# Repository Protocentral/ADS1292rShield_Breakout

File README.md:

ProtoCentral ADS1292R ECG/respiration shield and breakout board 
================================

[  
Dont have it yet? But one here: ADS1292R ECG/Respiration Shield for Arduino- v2 (PC-4128)](https://protocentral.com/product/ads1292r-ecg-respiration-shield-for-arduino-v2/)

[  
Dont have it yet? But one here: ADS1292R ECG/Respiration Breakout for Arduino- v3 (PC-4116)](https://protocentral.com/product/ads1292r-ecg-respiration-breakout-kit/)

The Arduino library for this product is now available in the **[ProtoCentral ADS1292R Arduino Library repo](https://github.com/Protocentral/protocentral-ads1292r-arduino)**

**Breakout v4:** KiCad design files and the schematic PDF are in [`hardware/breakout/v4`](hardware/breakout/v4). v4 has a new 10-pin host header (CS, MOSI, SCK, MISO, DRDY, START, RST, CLK, VCC, GND) with the ADS1292R clock brought out, so the pinout below applies to v3 only. Earlier revisions remain in `hardware/breakout` and `hardware/shield`.

Easily monitor ECG and respiration using your Arduino with this plug-in shield. The version 2 of this product adds a new SPI pin header making it compatible with newer Arduino devices including the Arduino Yun and 3.5mm connector for the electrodes. We now include the electrodes and cable also with the shield

Just plug it into an Arduino and you're ready to go. The 3.5 mm circular connector provides an easy way to connect electodes to the shield. The other end of this cable has snaps for standard ECG electrodes. We also include a pakc of 10 disposable EG electrodes. It accepts two ECG electrodes and one Driven Right Leg (DRL) electrode for common mode noise reduction. 

Another interesting feature of this shield is that you can also measure the respiratory activity using the same two electrodes connected to the shield. The ADS1292R uses a method known as impedance pneumography to measure respiration using the changes in chest impedance caused during respiration. 

Features:
----------
* ADS1292R Analog Front End IC
* Onboard 3.3V voltage regulator for low noise
* Onboard logic level transalators for Arduino interface
* Prototyping area for adding addtional components

Includes:
----------
* ADS1292R Arduino shield
* Electrode cable with 3.5mm connector and ECG electrodes connectors
* Pack of 10 disposable stick-on ECG electrodes.

Connecting the shield to your Arduino
-------------------------------------
Connect the ECG/Respiration shield to the Arduino by stacking it on top of your Arduino. This shield uses the SPI interface  to communicate with the Arduino. Since this includes the ICSP header, which is used on newer Arduinos for SPI communication,  this shield is also compatible newer Arduino boards such as the Arduino Yun and Due.
 
Wiring the Breakout to your Arduino
------------------------------------
 If you have bought the breakout the connection with the Arduino board is as follows:
 
|ads1292r pin label| Arduino Connection   |Pin Function      |
|----------------- |:--------------------:|-----------------:|
| VDD              | +5V                  |  Supply voltage  |             
| PWDN/RESET       | D4                   |  Reset           |
| START            | D5                   |  Start Input     |
| DRDY             | D6                   |  Data Ready Outpt|
| CS               | D7                   |  Chip Select     |
| MOSI             | D11                  |  Slave In        |
| MISO             | D12                  |  Slave Out       |
| SCK              | D13                  |  Serial Clock    |
| GND              | Gnd                  |  Gnd             |
 
Installing the Arduino libraries 
---------------------------------
Arduino library for this boards is now available at https://github.com/Protocentral/protocentral-ads1292r-arduino or from the Arduino Library Manager inside the Arduino IDe. 

If you have correctly installed the libraries, the example sketeches should now be available from within Arduino at File-->Examples-->ProtoCentral ADS1292R library.

Using the ProtoCentral OpenView GUI
-----------------------------------

The GUI for visualizing the ECG and Respiration as well as parameters like Heart rate and Respiration rate is written in Processing, based on Java and is cross-compilable across platforms. 
 
Java 8 is required on all platforms for running the processing-based GUI application. You can download Java for your platform from the [Official Java website](https://java.com/en/download/).

You can download and install [ProtoCentral OpenView](https://github.com/Protocentral/protocentral_openview) from here: https://github.com/Protocentral/protocentral_openview

Connecting the ECG Electrodes
------------------------------
 A 3-electrode cable along with a standard stereo jack is provided along with the shield to connect the electrodes to the     shield. The electrode input connector is highlighted in the below picture.
 
 The other side of the electrode connector would connect to snap-on electrodes attached to the body. For testing purposes,    you can use an ECG simulator to provide inputs to the board. 

 Warning:
 When connecting the electodes to the body, it is safer to disconnect the mains power source to the Arduino. For example, if  you are using the Arduino along with a laptop, disconnecting the battery charger from the laptop would be a safe option.
 
Placing the Electrodes on the body
---------------------------------

License Information
===================
This product is open source! 

Both, our hardware and software are open source and licensed under the following licenses:

Hardware
---------

**All hardware is released under the [CERN-OHL-P v2](https://ohwr.org/cern_ohl_p_v2.txt)** license.

Copyright CERN 2020.

This source describes Open Hardware and is licensed under the CERN-OHL-P v2.

You may redistribute and modify this documentation and make products
using it under the terms of the CERN-OHL-P v2 (https:/cern.ch/cern-ohl).
This documentation is distributed WITHOUT ANY EXPRESS OR IMPLIED
WARRANTY, INCLUDING OF MERCHANTABILITY, SATISFACTORY QUALITY
AND FITNESS FOR A PARTICULAR PURPOSE. Please see the CERN-OHL-P v2
for applicable conditions

Software
--------

**All software is released under the MIT License(http://opensource.org/licenses/MIT).**

THE SOFTWARE IS PROVIDED "AS IS", WITHOUT WARRANTY OF ANY KIND, EXPRESS OR IMPLIED, INCLUDING BUT NOT LIMITED TO THE WARRANTIES OF MERCHANTABILITY, FITNESS FOR A PARTICULAR PURPOSE AND NONINFRINGEMENT. IN NO EVENT SHALL THE AUTHORS OR COPYRIGHT HOLDERS BE LIABLE FOR ANY CLAIM, DAMAGES OR OTHER LIABILITY, WHETHER IN AN ACTION OF CONTRACT, TORT OR OTHERWISE, ARISING FROM, OUT OF OR IN CONNECTION WITH THE SOFTWARE OR THE USE OR OTHER DEALINGS IN THE SOFTWARE.

Documentation
-------------
**All documentation is released under [Creative Commons Share-alike 4.0 International](http://creativecommons.org/licenses/by-sa/4.0/).**

You are free to:

* Share — copy and redistribute the material in any medium or format
* Adapt — remix, transform, and build upon the material for any purpose, even commercially.
The licensor cannot revoke these freedoms as long as you follow the license terms.

Under the following terms:

* Attribution — You must give appropriate credit, provide a link to the license, and indicate if changes were made. You may do so in any reasonable manner, but not in any way that suggests the licensor endorses you or your use.
* ShareAlike — If you remix, transform, or build upon the material, you must distribute your contributions under the same license as the original.

Please check [*LICENSE.md*](LICENSE.md) for detailed license descriptions.

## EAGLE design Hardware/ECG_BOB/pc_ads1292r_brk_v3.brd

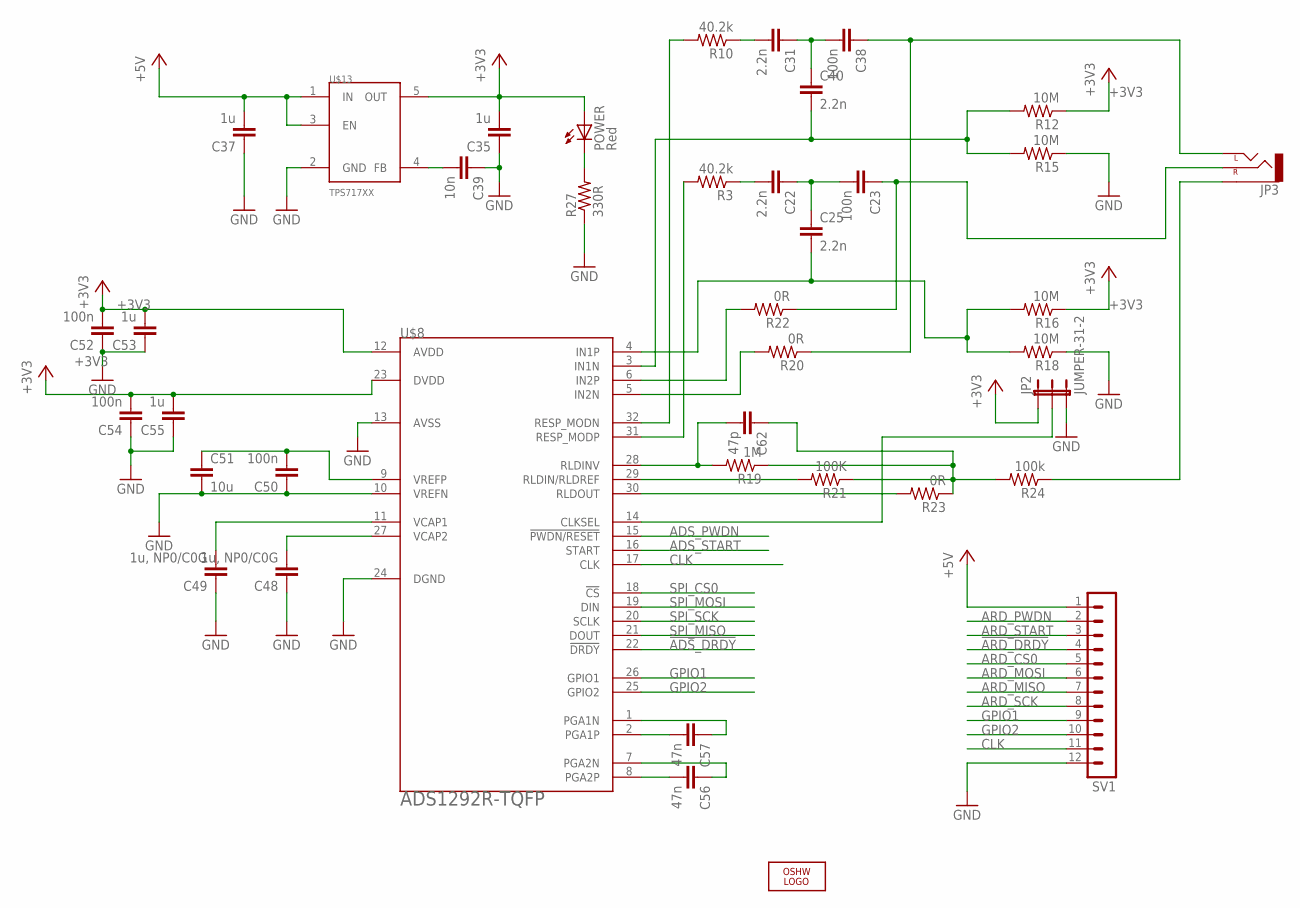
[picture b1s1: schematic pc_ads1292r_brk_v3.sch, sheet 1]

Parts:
C22, C25, C31, C40: 2.2n; C0402
C23, C38, C50, C52, C54: 100n; C0402
C35, C37, C53, C55: 1u; C0402
C39: 10n; C0402
C48, C49: 1u, NP0/C0G; C0402
C51: 10u; C0603
C56, C57: 47n; C0402
C62: 47p; C0402
JP2: JUMPER-31-2; SJ_3_PASTE1&2
JP3: AUDIO-JACKSMD2; AUDIO-JACK-3.5MM-SMD
LOGO1: OSHW_LOGO_FILLX0100-NT; OSHW_FILLX100_NOTEXT
POWER: Red; CHIPLED_0603
R3, R10: 40.2k; R0402
R12, R15, R16, R18: 10M; R0402
R19: 1M; R0402
R20, R22, R23: 0R; R0402
R21: 100K; R0402
R24: 100k; R0402
R27: 330R; R0402
SV1: MA12-1
U$8: ADS1292R-TQFP; SQFP-S-5X5-32
U$13: TPS717XX; SC70-5

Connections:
!ADS_DRDY: U$8.22 (!DRDY); also elsewhere on the board
!ARD_DRDY: SV1.4; also elsewhere on the board
+3V3: C35.2, C52.2, C53.2, C54.2, C55.2, JP2.1, POWER.A, R12.1, R16.1, U$8.12 (AVDD), U$8.23 (DVDD), U$13.5 (OUT); also elsewhere on the board
ADS_PWDN: U$8.15 (!PWDN/RESET); also elsewhere on the board
ADS_START: U$8.16 (START); also elsewhere on the board
ARD_CS0: SV1.5; also elsewhere on the board
ARD_MISO: SV1.7; also elsewhere on the board
ARD_MOSI: SV1.6; also elsewhere on the board
ARD_PWDN: SV1.2; also elsewhere on the board
ARD_SCK: SV1.8; also elsewhere on the board
ARD_START: SV1.3; also elsewhere on the board
CLK: SV1.11, U$8.17 (CLK)
GND: C35.1, C37.1, C39.1, C48.1, C49.1, C50.1, C51.2, C52.1, C53.1, C54.1, C55.1, JP2.3, R15.1, R18.1, R27.1, SV1.12, U$8.10 (VREFN), U$8.13 (AVSS), U$8.24 (DGND), U$13.2 (GND); also elsewhere on the board
GPIO1: SV1.9, U$8.26 (GPIO1)
GPIO2: SV1.10, U$8.25 (GPIO2)
unnamed: POWER.C, R27.2
unnamed: R3.2, U$8.31 (RESP_MODP)
unnamed: C22.2, R3.1
unnamed: C22.1, C23.2, C25.1
unnamed: R22.2, U$8.6 (IN2P)
unnamed: R20.2, U$8.5 (IN2N)
unnamed: C48.2, U$8.27 (VCAP2)
unnamed: R10.2, U$8.32 (RESP_MODN)
unnamed: C31.2, R10.1
unnamed: C31.1, C38.2, C40.1
unnamed: C38.1, JP3.TIP (LEFT), R20.1
unnamed: C40.2, R12.2, R15.2, U$8.3 (IN1N)
unnamed: C25.2, R16.2, R18.2, U$8.4 (IN1P)
unnamed: R21.2, U$8.29 (RLDIN/RLDREF)
unnamed: C62.2, R19.2, U$8.28 (RLDINV)
unnamed: C62.1, R19.1, R21.1, R23.1, R24.2
unnamed: C49.2, U$8.11 (VCAP1)
unnamed: C56.2, U$8.8 (PGA2P)
unnamed: C56.1, U$8.7 (PGA2N)
unnamed: C50.2, C51.1, U$8.9 (VREFP)
unnamed: C57.2, U$8.2 (PGA1P)
unnamed: C57.1, U$8.1 (PGA1N)
unnamed: C23.1, JP3.RING (RIGHT), R22.1
unnamed: R23.2, U$8.30 (RLDOUT)
unnamed: JP3.SLEEVE, R24.1
unnamed: JP2.2, U$8.14 (CLKSEL)
unnamed: C39.2, U$13.4 (FB)
SPI_CS0: U$8.18 (!CS); also elsewhere on the board
SPI_MISO: U$8.21 (DOUT); also elsewhere on the board
SPI_MOSI: U$8.19 (DIN); also elsewhere on the board
SPI_SCK: U$8.20 (SCLK); also elsewhere on the board

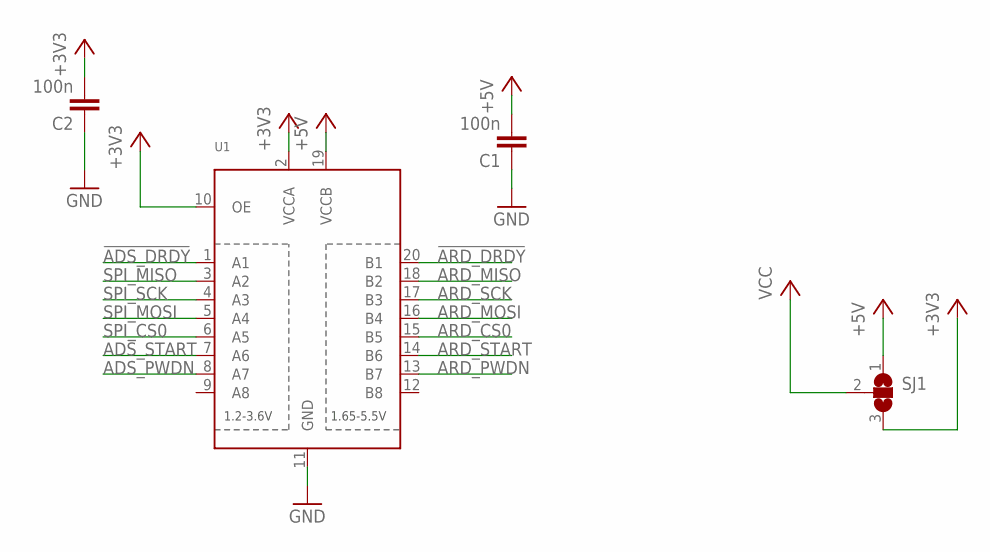
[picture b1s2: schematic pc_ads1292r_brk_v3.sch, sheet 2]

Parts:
C1, C2: 100n; C0402
SJ1: SJ2W; SJ_2
U1: TXB0108PWR; TSSOP20

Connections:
!ADS_DRDY: U1.1 (A1); also elsewhere on the board
!ARD_DRDY: U1.20 (B1); also elsewhere on the board
+3V3: C2.2, SJ1.3, U1.2 (VCCA), U1.10 (OE); also elsewhere on the board
ADS_PWDN: U1.8 (A7); also elsewhere on the board
ADS_START: U1.7 (A6); also elsewhere on the board
ARD_CS0: U1.15 (B5); also elsewhere on the board
ARD_MISO: U1.18 (B2); also elsewhere on the board
ARD_MOSI: U1.16 (B4); also elsewhere on the board
ARD_PWDN: U1.13 (B7); also elsewhere on the board
ARD_SCK: U1.17 (B3); also elsewhere on the board
ARD_START: U1.14 (B6); also elsewhere on the board
GND: C1.1, C2.1, U1.11 (GND); also elsewhere on the board
SPI_CS0: U1.6 (A5); also elsewhere on the board
SPI_MISO: U1.3 (A2); also elsewhere on the board
SPI_MOSI: U1.5 (A4); also elsewhere on the board
SPI_SCK: U1.4 (A3); also elsewhere on the board

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
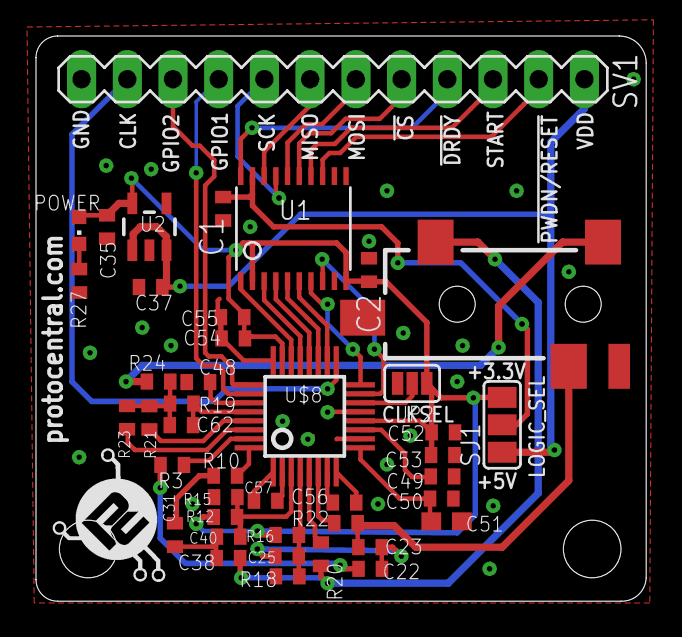
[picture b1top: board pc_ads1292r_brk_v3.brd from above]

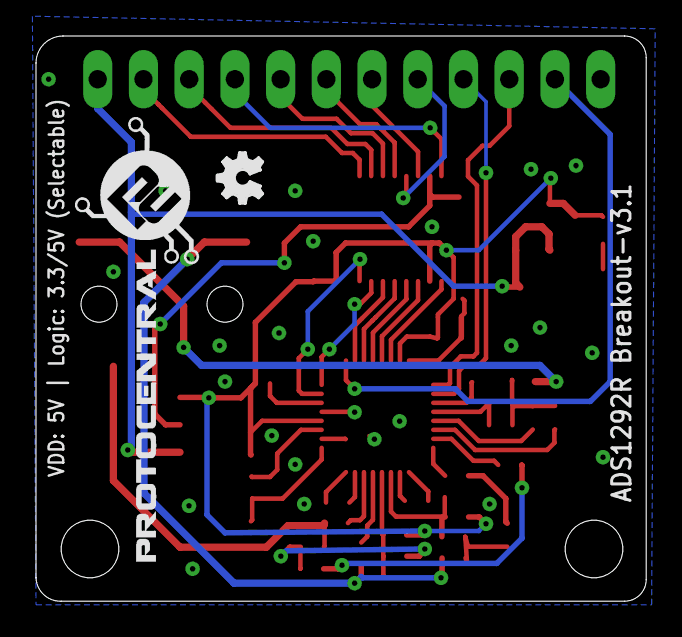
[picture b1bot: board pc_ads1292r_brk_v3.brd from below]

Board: 4 copper layers, 33.9 x 31.4 mm, 45 parts (2 on the bottom side), 47 nets.

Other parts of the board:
U2: AP2112K-3.3V; SOT23-5
U$1: PROTY-LOGO; LOGO-PROTY
U$2: PROTY_WITH_TEXT

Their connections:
+3V3: U2.5; also elsewhere on the board
GND: U2.2; also elsewhere on the board

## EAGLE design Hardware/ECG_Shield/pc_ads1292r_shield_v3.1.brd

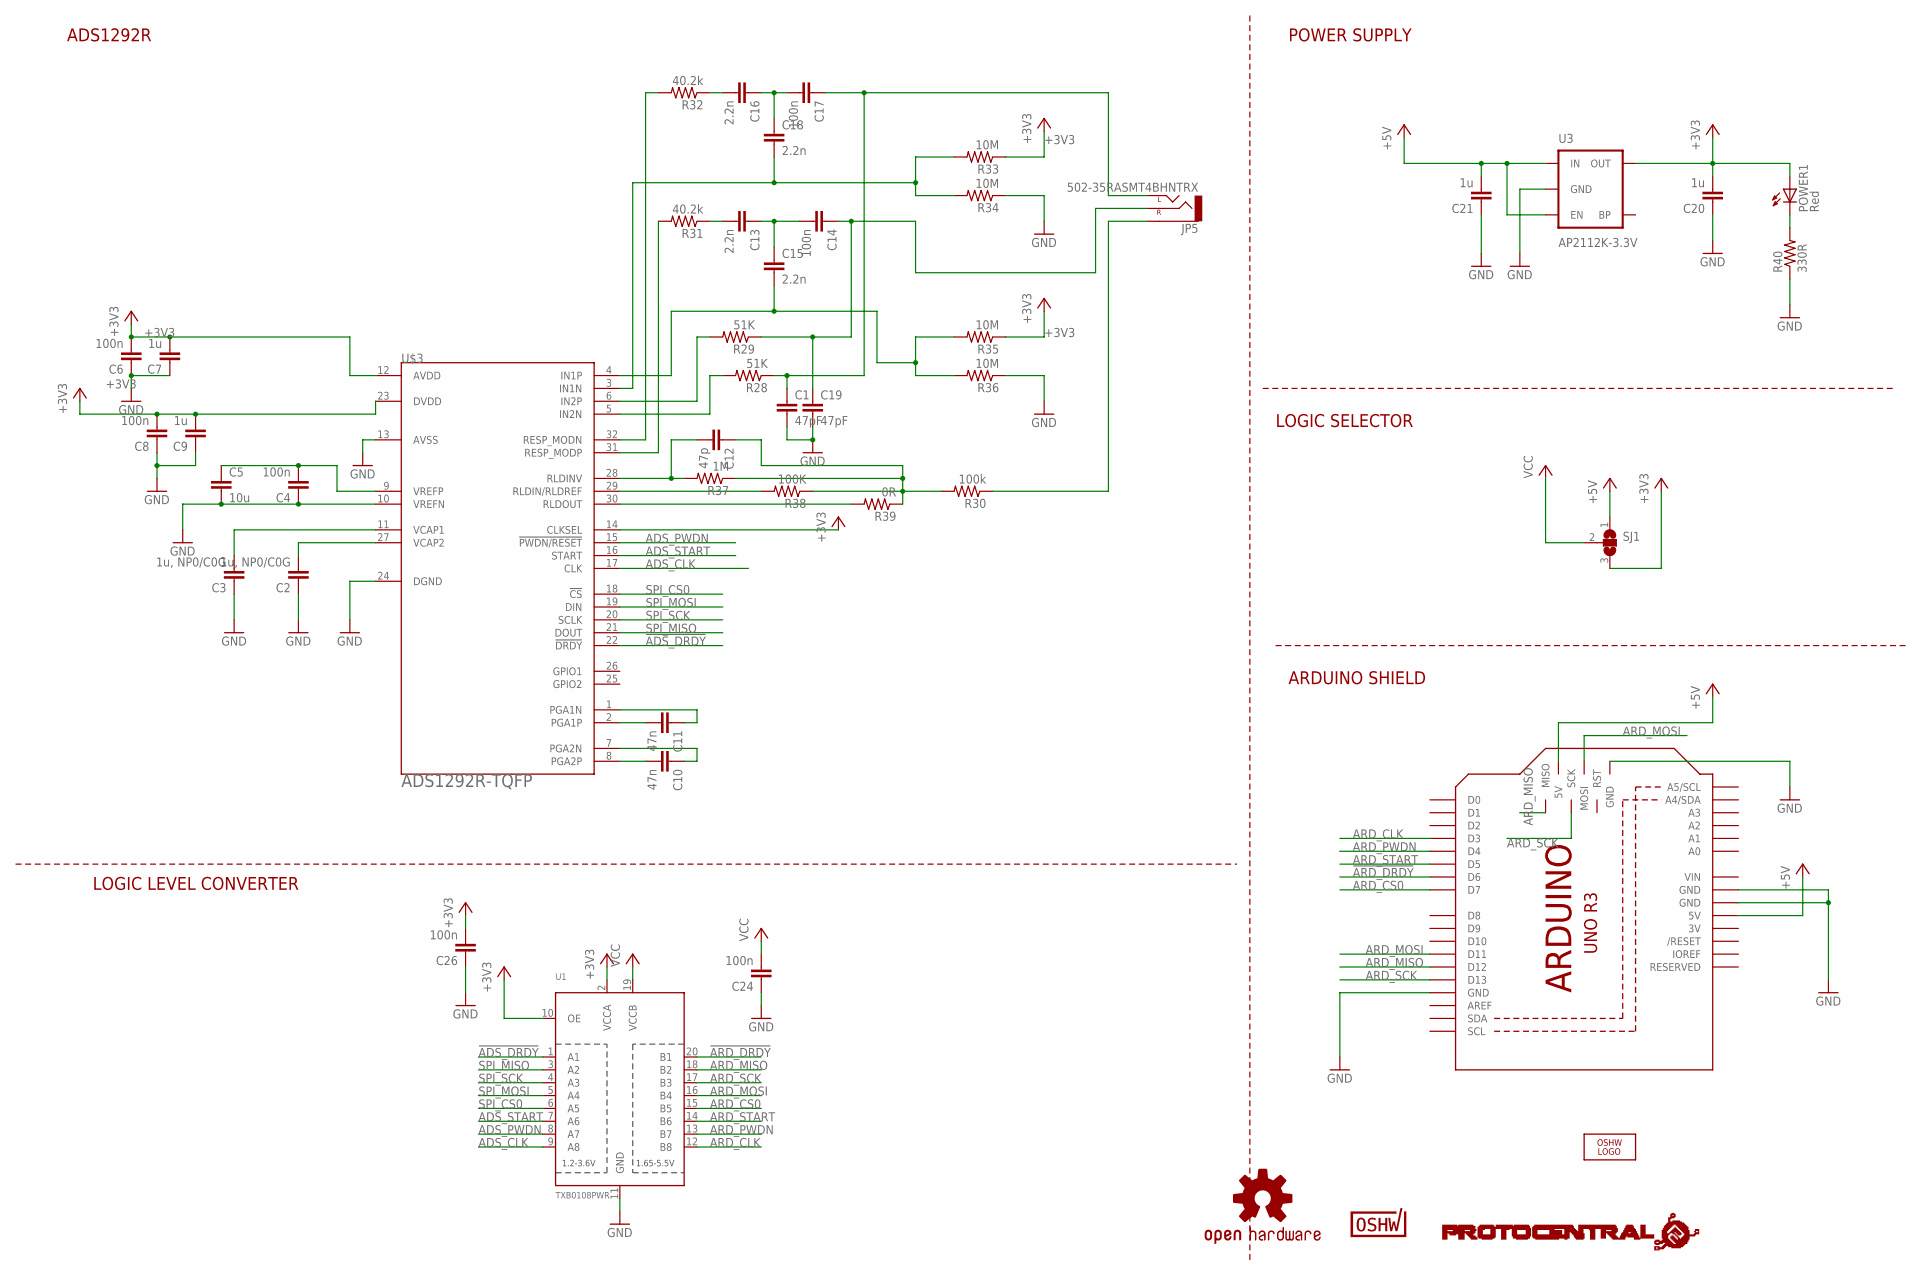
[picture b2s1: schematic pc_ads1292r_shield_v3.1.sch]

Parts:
C1, C19: 47pF; C0402
C2, C3: 1u, NP0/C0G; C0402
C4, C6, C8, C14, C17, C24, C26: 100n; C0402
C5: 10u; C0603
C7, C9, C20, C21: 1u; C0402
C10, C11: 47n; C0402
C12: 47p; C0402
C13, C15, C16, C18: 2.2n; C0402
JP5: 502-35RASMT4BHNTRX; AUDIO-JACK-3.5MM-SMD
LOGO1: OSHW_LOGO_FILLX0100-NT; OSHW_FILLX100_NOTEXT
M1: ARDUINO
POWER1: Red; CHIPLED_0603
R28, R29: 51K; R0402
R30: 100k; R0402
R31, R32: 40.2k; R0402
R33, R34, R35, R36: 10M; R0402
R37: 1M; R0402
R38: 100K; R0402
R39: 0R; R0402
R40: 330R; R0402
SJ1: SJ2W; SJ_2
U1: TXB0108PWR; TSSOP20
U3: AP2112K-3.3V; SOT23-5
U$1: CERT-SMALL; CERT-SMALL-SILK
U$3: ADS1292R-TQFP; SQFP-S-5X5-32
U$4: PROTY_LOGO_WITH_TEXT; PROTY_WITH_TEXT
U$6: OSHW-LOGOS; OSHW-LOGO-S

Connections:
3V: M1.3V
!ADS_DRDY: U1.1 (A1), U$3.22 (!DRDY)
!ARD_DRDY: M1.D6, U1.20 (B1)
+3V3: C6.2, C7.2, C8.2, C9.2, C20.2, C26.2, POWER1.A, R33.1, R35.1, SJ1.3, U1.2 (VCCA), U1.10 (OE), U3.5 (OUT), U$3.12 (AVDD), U$3.14 (CLKSEL), U$3.23 (DVDD)
+5V: C21.2, M1.5V, M1.5V_ICSP (5V), SJ1.1, U3.1 (IN), U3.3 (EN)
ADS_CLK: U1.9 (A8), U$3.17 (CLK)
ADS_PWDN: U1.8 (A7), U$3.15 (!PWDN/RESET)
ADS_START: U1.7 (A6), U$3.16 (START)
ARD_CLK: M1.D3, U1.12 (B8)
ARD_CS0: M1.D7, U1.15 (B5)
ARD_MISO: M1.D12, M1.MISO, U1.18 (B2)
ARD_MOSI: M1.D11, M1.MOSI, U1.16 (B4)
ARD_PWDN: M1.D4, U1.13 (B7)
ARD_SCK: M1.D13, M1.SCK, U1.17 (B3)
ARD_START: M1.D5, U1.14 (B6)
GND: C1.2, C2.1, C3.1, C4.1, C5.2, C6.1, C7.1, C8.1, C9.1, C19.2, C20.1, C21.1, C24.1, C26.1, M1.GND, M1.GND@1 (GND), M1.GND@2 (GND), M1.GND@3 (GND), R34.1, R36.1, R40.1, U1.11 (GND), U3.2 (GND), U$3.10 (VREFN), U$3.13 (AVSS), U$3.24 (DGND)
unnamed: C2.2, U$3.27 (VCAP2)
unnamed: C3.2, U$3.11 (VCAP1)
unnamed: C4.2, C5.1, U$3.9 (VREFP)
unnamed: C10.2, U$3.8 (PGA2P)
unnamed: C10.1, U$3.7 (PGA2N)
unnamed: C11.2, U$3.2 (PGA1P)
unnamed: C11.1, U$3.1 (PGA1N)
unnamed: C14.1, C19.1, JP5.RING (RIGHT), R29.1
unnamed: R39.2, U$3.30 (RLDOUT)
unnamed: JP5.SLEEVE, R30.1
unnamed: R31.2, U$3.31 (RESP_MODP)
unnamed: C13.2, R31.1
unnamed: C13.1, C14.2, C15.1
unnamed: R32.2, U$3.32 (RESP_MODN)
unnamed: C16.2, R32.1
unnamed: C16.1, C17.2, C18.1
unnamed: C1.1, C17.1, JP5.TIP (LEFT), R28.1
unnamed: C18.2, R33.2, R34.2, U$3.3 (IN1N)
unnamed: C15.2, R35.2, R36.2, U$3.4 (IN1P)
unnamed: R29.2, U$3.6 (IN2P)
unnamed: R28.2, U$3.5 (IN2N)
unnamed: C12.2, R37.2, U$3.28 (RLDINV)
unnamed: R38.2, U$3.29 (RLDIN/RLDREF)
unnamed: C12.1, R30.2, R37.1, R38.1, R39.1
unnamed: POWER1.C, R40.2
SPI_CS0: U1.6 (A5), U$3.18 (!CS)
SPI_MISO: U1.3 (A2), U$3.21 (DOUT)
SPI_MOSI: U1.5 (A4), U$3.19 (DIN)
SPI_SCK: U1.4 (A3), U$3.20 (SCLK)
VCC: C24.2, SJ1.2, U1.19 (VCCB)
VIN: M1.VIN

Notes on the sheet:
POWER SUPPLY
LOGIC SELECTOR
ARDUINO SHIELD
LOGIC LEVEL CONVERTER
ADS1292R

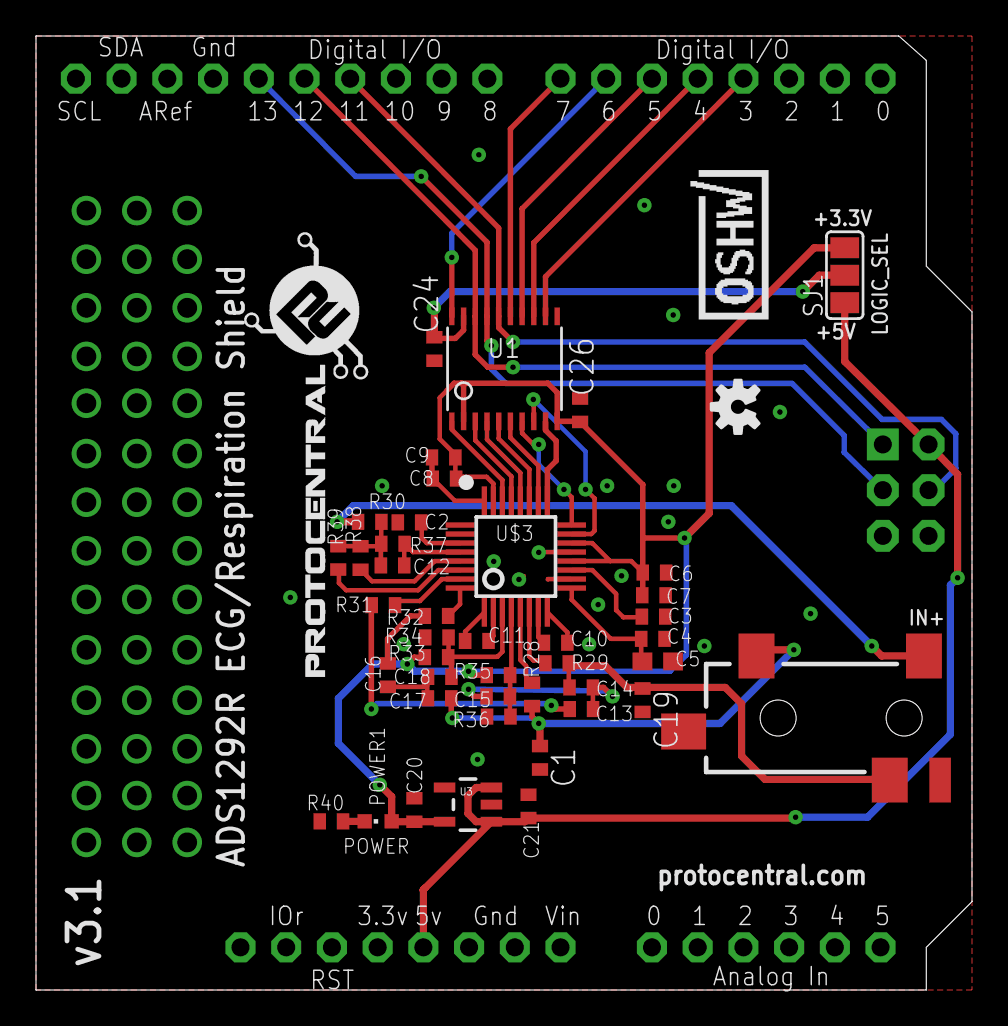
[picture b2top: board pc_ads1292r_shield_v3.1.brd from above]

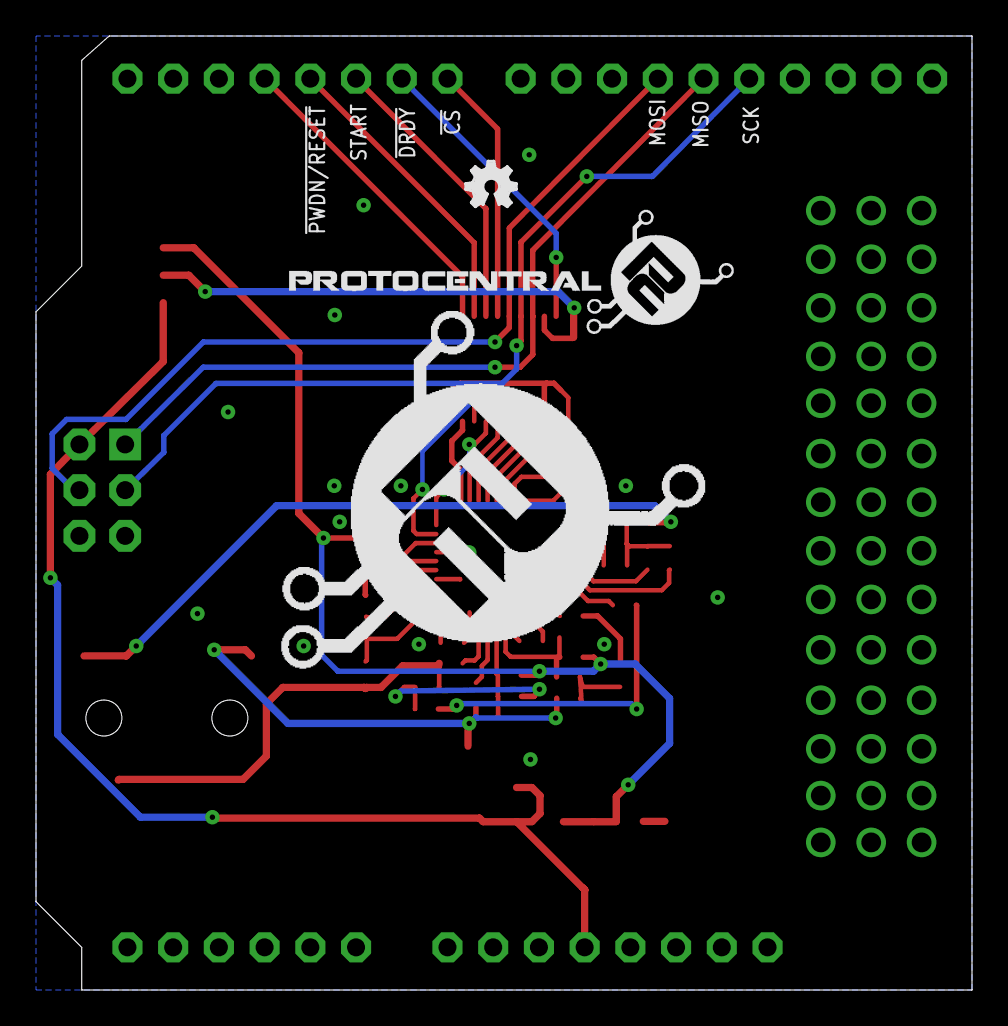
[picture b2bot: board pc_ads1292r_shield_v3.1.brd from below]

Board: 4 copper layers, 52.0 x 53.0 mm, 49 parts (3 on the bottom side), 45 nets.

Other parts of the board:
U$2: PROTY-LOGO-LARGE
U$5: PROTY_WITH_TEXT

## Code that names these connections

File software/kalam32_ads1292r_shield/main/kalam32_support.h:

/* Arduino Pin-out mapping */

#define PIN_NUM_0   17
#define PIN_NUM_1   14
#define PIN_NUM_2   13
#define PIN_NUM_4   2
#define PIN_NUM_5   16
#define PIN_NUM_6   26
#define PIN_NUM_7   17
#define PIN_NUM_8   25
#define PIN_NUM_10  12
#define PIN_NUM_11  23
#define PIN_NUM_12  19
#define PIN_NUM_13  18

#define PIN_NUM_A0  35
#define PIN_NUM_A1  34
#define PIN_NUM_A2  36
#define PIN_NUM_A3  39

#define PIN_I2C_SDA  21
#define PIN_I2C_SCL  22

#define PIN_SPI_CS   25
#define PIN_SPI_MOSI 23
#define PIN_SPI_MISO 19
#define PIN_SPI_SCK  18

void kalam32_uart_init(void);
void kalam_wifi_init(void);

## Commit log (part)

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2015-10-06 :tada: Added .gitattributes & .gitignore files
2015-10-06 ECGShield/breakout
2015-10-22 Design File
2015-10-22 datasheet
2015-10-30 Brainbay setup and config file
2016-05-18 Included Processing Sketch for ADS1292rShield_Breakout
2016-05-18 Removed Processing
2016-05-18 Processing Libraries
2016-05-18 Processing Sketch
2016-06-15 added arduino processing sketch
2016-06-16 Final Output
2016-06-16 Updated Libraries
2016-07-02 Libraries
2016-08-23 Added processing sketch for Arduino
2016-10-14 Processing Code
2016-10-14 Arduino Library
2016-11-18 Added license information
2016-11-18 Updated License information
2016-12-01 added new design file
2017-02-20 updated sketch
2017-02-20 updated skecth
2017-03-20 Changed folder structure with new updated GUI
2017-03-20 updated the links, and images
2017-03-20 Updated license information in Readme
2017-04-13 updated image
2017-04-21 Added Kalam32 example code
2017-04-22 Added GUI for Kalam32 TCP client
2017-04-25 Added mDNS Support
2017-04-25 Updated TCP GUI to support Kalam32 mDNS
2017-06-29 added design pdf file for v3 breakout
2017-06-30 added design file for v3
2017-08-22 Added Heart rate algorithm
    Added filter function, Heart rate calculation.
2020-10-21 Update README.md
    Edited Readme file
2020-10-25 Replaced images and links in README.md
2020-10-30 reorganised
2020-10-30 fixed indentation
2020-10-31 disabled algos for respiration
2020-12-31 Removed existing GUI and Arduino library (moved)
2020-12-31 Renamed hardware folder
2021-03-26 Updated License

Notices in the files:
README.md:
CC-BY-SA-4.0
parts and their libraries:
SparkFun-Connectors: Licensing: Creative Commons ShareAlike 4.0 International - https://creativecommons.org/licenses/by-sa/4.0
